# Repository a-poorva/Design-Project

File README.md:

# Design-Project

Design Skills Project (Variable Light Intensity)

Functional Specifications

1. LED light that is button-activated to switch between the following operating modes:
a. Off
b. Brightest
c. Intermediate Brightness
d. Least Bright
e. Flashing @ 2 Hz
2. Self-contained device with LED and button exposed.

Extra credit possibilities:
1. Battery life indicator
2. Waterproof enclosure
3. You tell us!

Constraints
1. Run on single battery up to 9 V
2. Electronics connected to a single PCB (can be single- or double-sided)
3. Cannot weight more than 1 lb
4. Cannot have a single dimension > 6 in
5. Cannot cost more than $50 to duplicate unit
6. Battery must be easily replaceable

Evaluation
1. Minimize weight
2. Minimize size
3. Maximize Brightest mode
4. Minimize power draw / maximize battery life
5. Survive 3 foot drop with battery installed

Create-and-maintain a GitHub project repository to maintain version history of:
1. Mechanical CAD (PDFs + more)
2. Electronic CAD (PDFs + more)
3. Software
4. Testing data
5. Design history / notes
6. Specification sheets
7. Usage notes (README.md)
8. Kanban board / Issues / Milestones

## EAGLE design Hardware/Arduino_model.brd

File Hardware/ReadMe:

Components used include:

1. Arduino Uno --> The PCB here is not routed as I used a protoboard. I have laid out the components as it might look on the shield.
2. Pushbutton - Adafruit
3. Resistors - R1, R2 -0402-01/16W-1%, SparkFun (100k)
4. Battery - G1, AB9V
5. LED - LED2, 5MM, Adafruit
6. Arduino Nano --> The PCB here is routed as I etched this board.

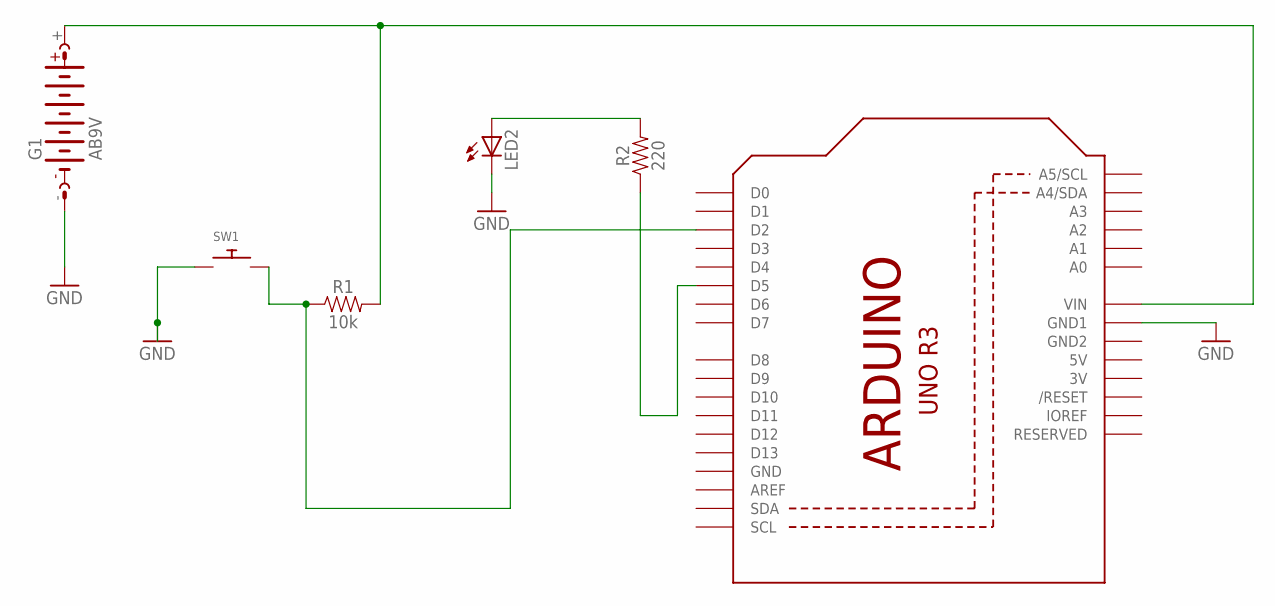
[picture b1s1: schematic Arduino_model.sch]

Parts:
G1: AB9V
LED2: LED5MM
R1: 10k; AXIAL-0.1
R2: 220; 0603
SW1: SWITCH_PUSHBUTTONEVQ-PE; TACT_PANA-EVQ
U1: ARDUINOR3-DIMENSION; ARDUINOR3

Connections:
3V: U1.3V
5V: U1.5V
GND: G1.-, LED2.K (C), SW1.P$1, U1.GND, U1.GND1
GND2: U1.GND2
unnamed: G1.+, R1.P$2 (2), U1.VIN
unnamed: R1.P$1 (1), SW1.P$2, U1.D2
unnamed: R2.1, U1.D5
unnamed: LED2.A, R2.2

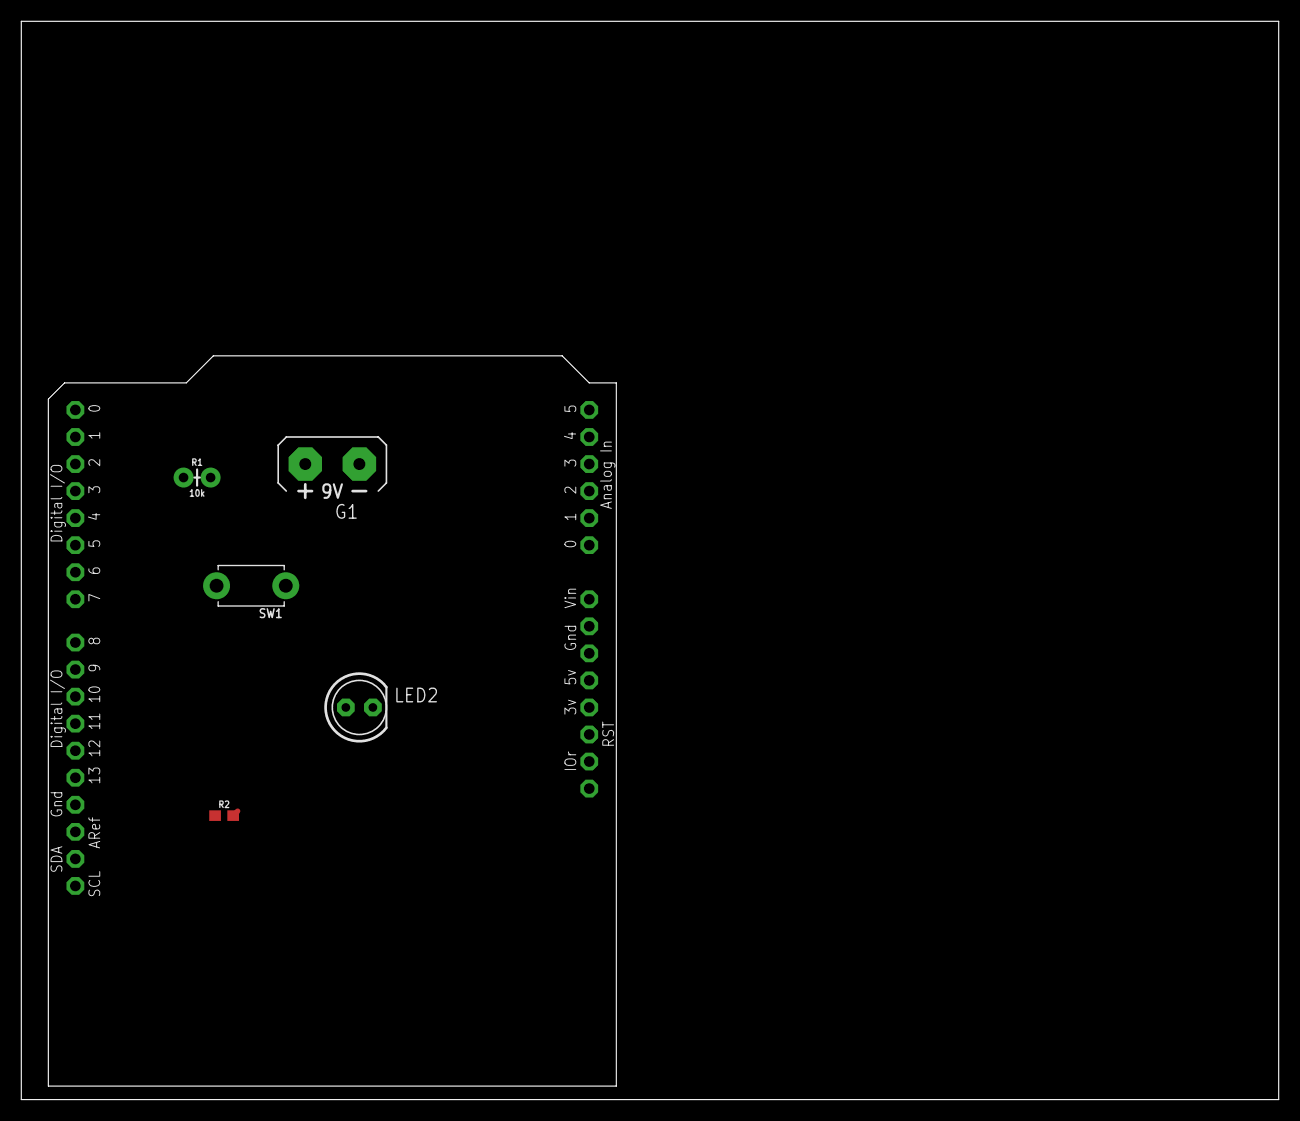
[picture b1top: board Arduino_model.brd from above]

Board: 2 copper layers, 118.1 x 101.3 mm, 6 parts (0 on the bottom side), 5 nets.

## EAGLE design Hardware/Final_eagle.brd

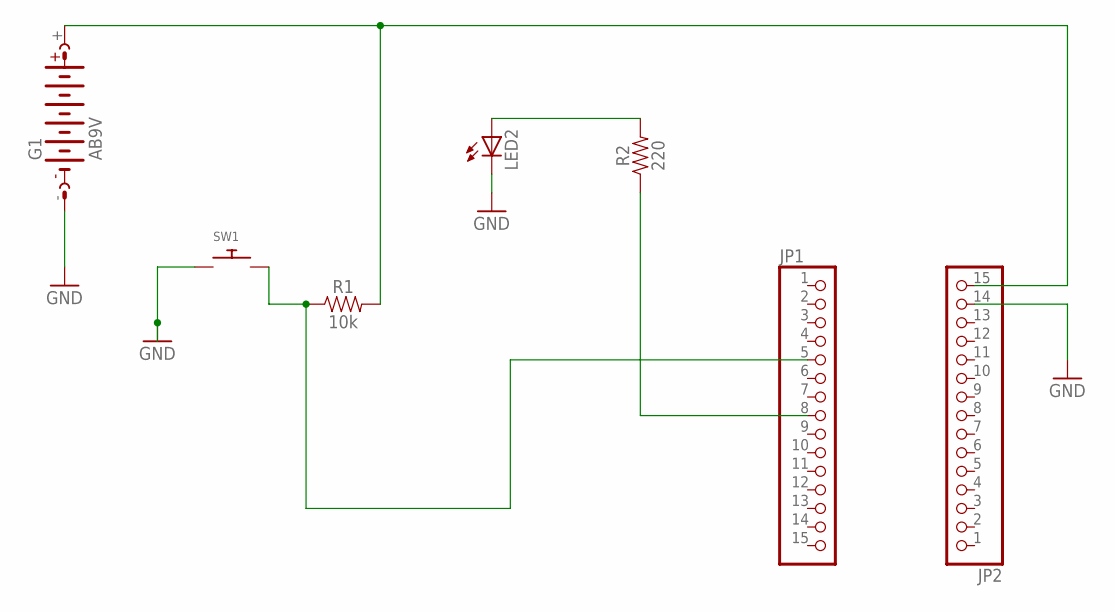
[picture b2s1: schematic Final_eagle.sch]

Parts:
G1: AB9V
JP1, JP2: PINHD-1X15; 1X15
LED2: LED5MM
R1: 10k; AXIAL-0.1
R2: 220; 0603
SW1: SWITCH_PUSHBUTTONEVQ-PE; TACT_PANA-EVQ

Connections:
GND: G1.-, JP2.14, LED2.K (C), SW1.P$1
unnamed: G1.+, JP2.15, R1.P$2 (2)
unnamed: JP1.5, R1.P$1 (1), SW1.P$2
unnamed: JP1.8, R2.1
unnamed: LED2.A, R2.2

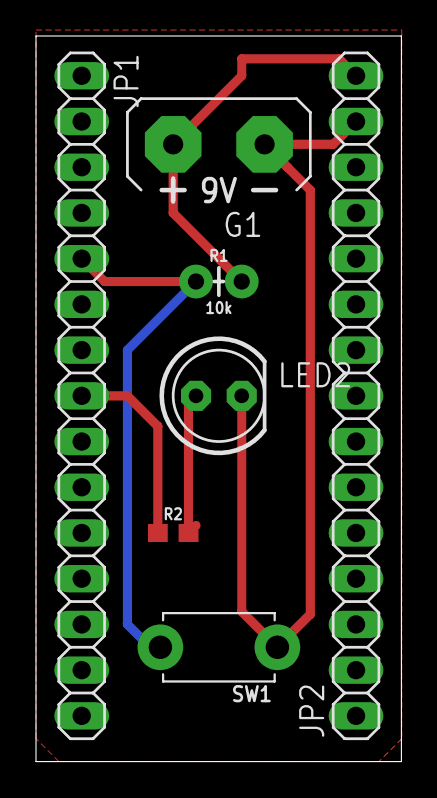
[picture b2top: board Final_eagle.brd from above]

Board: 2 copper layers, 20.3 x 40.3 mm, 7 parts (0 on the bottom side), 5 nets.

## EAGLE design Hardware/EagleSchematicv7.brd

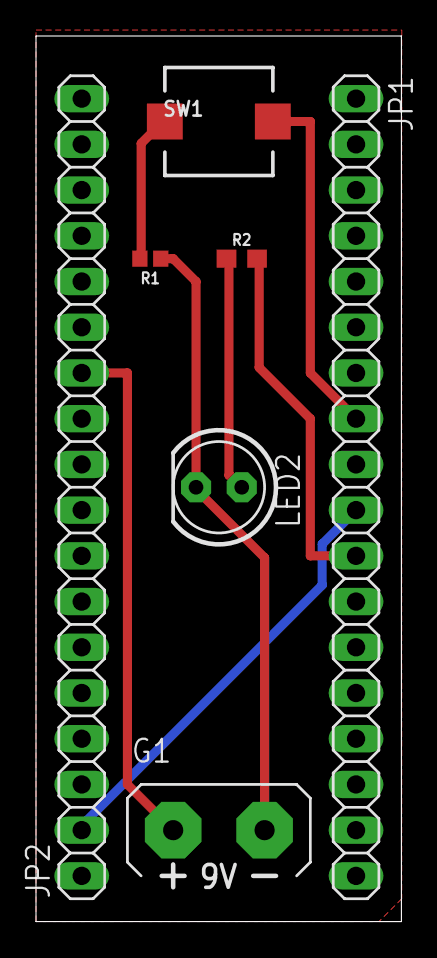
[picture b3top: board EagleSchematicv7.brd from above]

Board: 2 copper layers, 20.3 x 49.2 mm, 7 parts (0 on the bottom side), 7 nets.

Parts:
G1: AB9V
JP1, JP2: 1X18
LED2: LED5MM
R1: 100K; 0402
R2: 100; 0603
SW1: PUSHBUTTON_SMD_SJ

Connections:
GND: G1.-, LED2.K, R1.1
unnamed: G1.+, JP2.12
unnamed: R1.2, SW1.P$1
unnamed: JP1.8, SW1.P$2
unnamed: JP1.11, R2.2
unnamed: LED2.A, R2.1
unnamed: JP1.10, JP2.2

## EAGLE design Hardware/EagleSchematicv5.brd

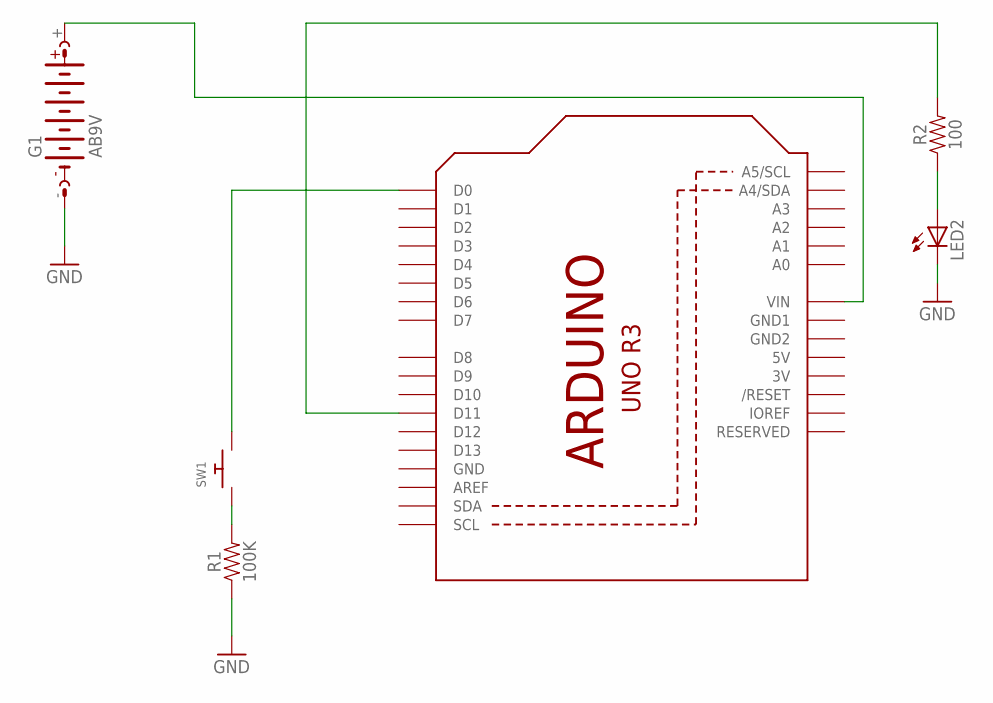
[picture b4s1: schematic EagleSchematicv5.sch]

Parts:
G1: AB9V
LED2: LED5MM
R1: 100K; 0402
R2: 100; 0603
SW1: SWITCH_PUSHBUTTONSOFTTOUCHSMD_SJ; PUSHBUTTON_SMD_SJ
U1: ARDUINOR3-BPLACE

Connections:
3V: U1.3V
5V: U1.5V
GND: G1.-, LED2.K (C), R1.1, U1.GND
GND1: U1.GND1
GND2: U1.GND2
unnamed: G1.+, U1.VIN
unnamed: R1.2, SW1.P$1
unnamed: SW1.P$2, U1.D0
unnamed: R2.2, U1.D11
unnamed: LED2.A, R2.1

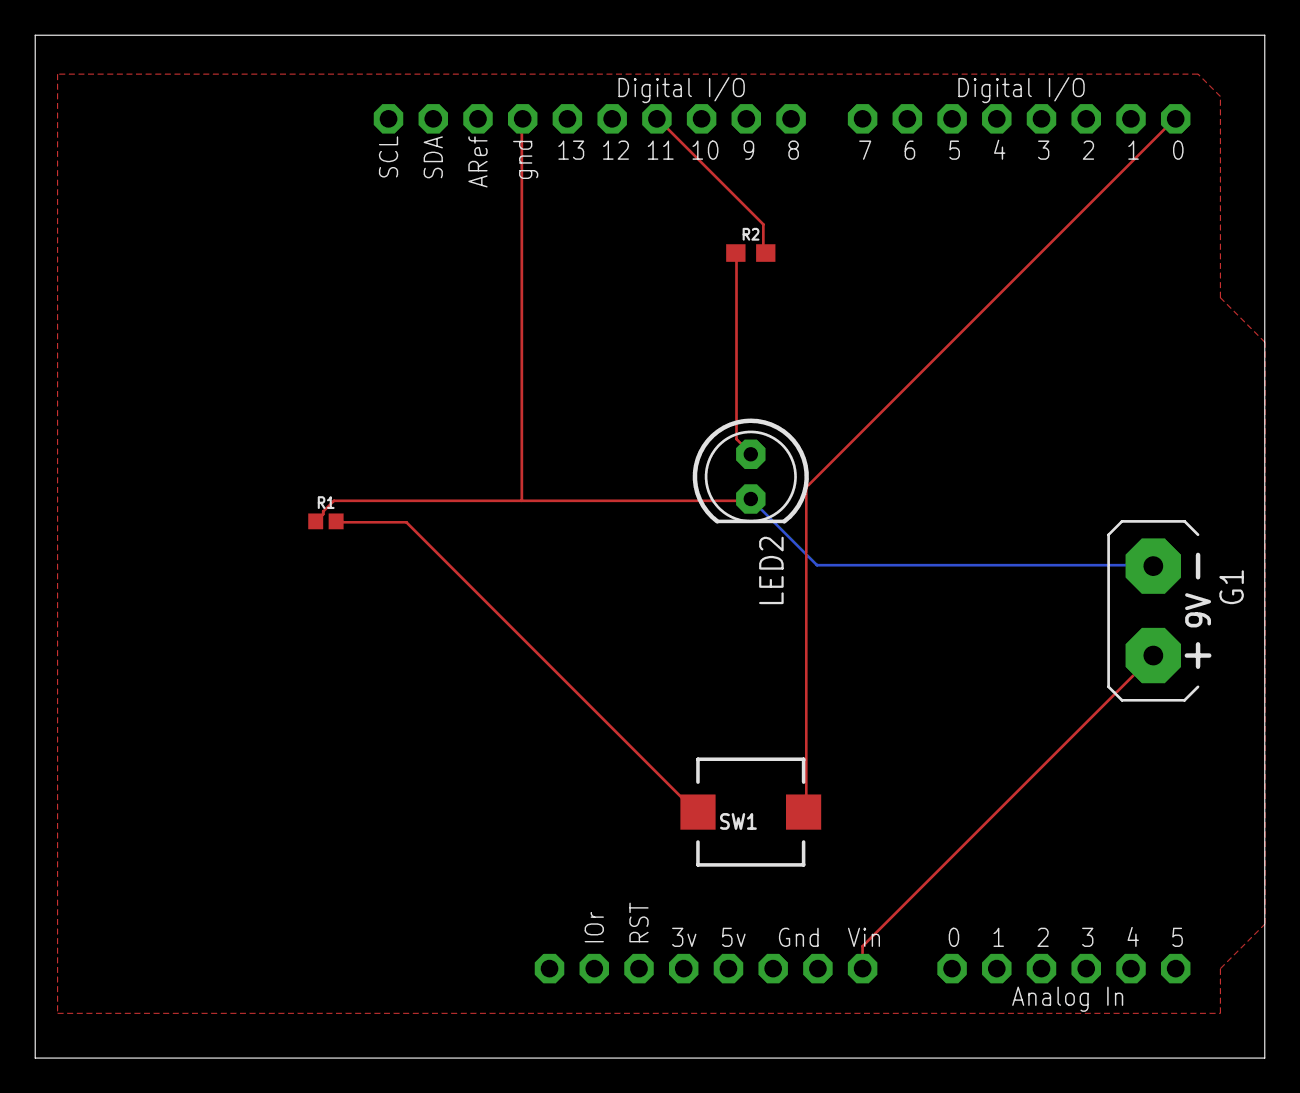
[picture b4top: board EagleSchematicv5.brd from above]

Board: 2 copper layers, 69.8 x 58.1 mm, 6 parts (0 on the bottom side), 6 nets.

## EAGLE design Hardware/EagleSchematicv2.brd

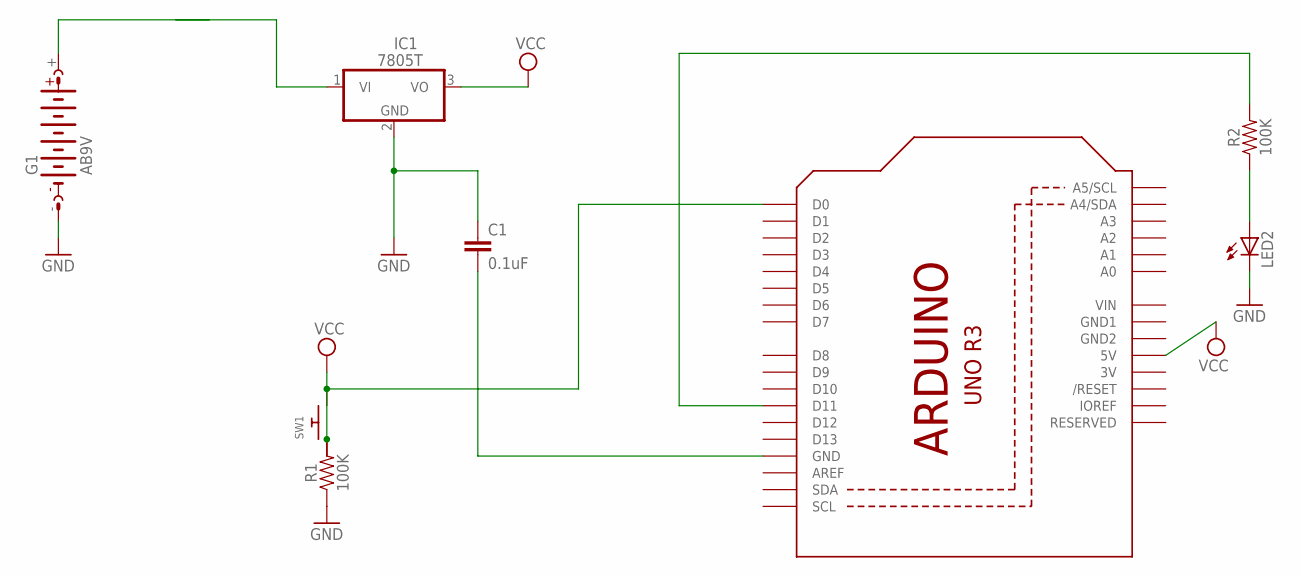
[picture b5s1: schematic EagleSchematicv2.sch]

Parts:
C1: 0.1uF; 0402
G1: AB9V
IC1: 7805T; TO220H
LED2: LED5MM
R1, R2: 100K; 0402
SW1: SWITCH_PUSHBUTTONSOFTTOUCHSMD_SJ; PUSHBUTTON_SMD_SJ
U1: ARDUINOR3-BPLACE

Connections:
3V: U1.3V
GND: C1.1, G1.-, IC1.2 (GND), LED2.K (C), R1.1
GND1: U1.GND1
GND2: U1.GND2
unnamed: C1.2, U1.GND
unnamed: R2.2, U1.D11
unnamed: LED2.A, R2.1
VCC: IC1.3 (VO), R1.2, SW1.P$2, U1.5V, U1.D0
VIN: U1.VIN

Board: 2 copper layers, 8 parts (0 on the bottom side), 5 nets, no tracks yet.

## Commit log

2018-10-18 Create Electrical
2018-10-18 Create Electronics
2018-10-30 Add files via upload
    Rough code v1
2018-11-01 LEDv3.2
2018-11-02 Electronic Schematic v2
2018-11-08 Add files via upload
    Schematics v1 using Eagle
2018-11-08 Schematic v1
    Hopefully with the right parts!
2018-11-08 Eagle Schematic v1
    Hopefully with the right parts!
2018-11-08 still working on it
2018-11-08 PCB design and layout
2018-11-08 in progress
2018-11-08 ready for review
2018-11-08 subject to change/review
2018-11-09 v2 - needs attention
2018-11-09 v3 - review
2018-11-13 to be reviewed
2018-11-18 see readme
2018-12-14 Please refer to readMe
2018-12-14 New box

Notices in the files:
parts and their libraries:
SparkFun-Resistors: Licensing: Creative Commons ShareAlike 4.0 International - https://creativecommons.org/licenses/by-sa/4.0
